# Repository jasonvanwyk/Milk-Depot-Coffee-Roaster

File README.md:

# Milk Depot Coffee Roaster - Precept Systems Project

## Client Information

| Field | Details |
|-------|---------|
| **Client Name** | Quenton (Milk Depot) |
| **Contact** | Via Jason van Wyk |
| **Project** | Coffee Roaster Temperature Monitoring System |

## Project Overview

Custom coffee roasting temperature monitoring system integrating Arduino-based 3-channel thermocouple interface with Artisan roasting software on Raspberry Pi 4. The system reads Bean Temperature (BT), Exhaust Temperature (ET), and Flame Temperature (FT) via MAX31855 amplifiers and displays real-time temperature curves with rate-of-rise calculations.

## Project Scope

1. **Arduino Firmware** - TC4 protocol emulator for 3-channel MAX31855 thermocouple reading
2. **Hardware Integration** - 3x custom K-type thermocouple probes with compression fittings, MAX31855 amplifiers, enclosure
3. **Software Configuration** - Artisan v3.4.0 setup on Raspberry Pi 4 with ArduinoTC4 device
4. **Calibration & Testing** - Probe calibration and first test roast

## Current Status

**See `STATUS.md` for detailed task tracking and current project status.**

### Quick Status
- **Phase:** Hardware Procurement
- **Software:** Complete and tested (firmware + Artisan)
- **Hardware:** Thermocouples on order from GPA Trading (PO P00041)

### Milestones
- [x] Git repository initialized
- [x] Artisan v3.4.0 installed on Raspberry Pi
- [x] Arduino TC4 firmware written and tested
- [x] Helper scripts created (compile, upload, detect, monitor)
- [x] Documentation complete
- [x] Custom thermocouple probes ordered (GPA Trading)
- [ ] Thermocouple probes delivered
- [ ] MAX31855 modules + remaining components procured
- [ ] Hardware assembly in enclosure
- [ ] Sensor calibration
- [ ] First test roast

## Hardware Summary

| Component | Status |
|-----------|--------|
| Raspberry Pi 4 | Owned, Artisan installed |
| Arduino UNO R3 | Owned, firmware tested |
| 3x Custom K-Type Probes | On order (GPA Trading, PO P00041) |
| 3x MAX31855 Modules | To be procured |
| ABS Enclosure | To be procured |
| SSD1306 OLED (optional) | To be procured |

## Temperature Channels

| Channel | Name | Description | Artisan Mapping |
|---------|------|-------------|-----------------|
| 1 | ET | Exhaust/Environment Temperature | Primary ET |
| 2 | BT | Bean Temperature | Primary BT |
| 3 | FT | Flame/Burner Temperature | Extra (ArduinoTC4_34) |

## Key Files

| File | Purpose |
|------|---------|
| `STATUS.md` | **Current project status and task tracking** |
| `RESUME.md` | Quick session resume context |
| `CLAUDE.md` | AI assistant project context |
| `correspondence/` | All client/supplier correspondence |
| `docs/` | Technical documentation and planning |
| `arduino-firmware/` | Arduino sketches (TC4 emulator, temp monitor, etc.) |
| `scripts/` | Helper scripts (compile, upload, detect, monitor) |

## Documentation

All technical documentation is in `docs/`:

| Document | Description |
|----------|-------------|
| [BOM.md](docs/BOM.md) | Bill of Materials with pricing |
| [WIRING.md](docs/WIRING.md) | Wiring diagrams and enclosure layout |
| [ARTISAN_INTEGRATION.md](docs/ARTISAN_INTEGRATION.md) | Artisan configuration guide |
| [SERIAL_PROTOCOL.md](docs/SERIAL_PROTOCOL.md) | TC4 serial communication protocol |
| [ARDUINO_CLI.md](docs/ARDUINO_CLI.md) | Arduino CLI workflow guide |
| [THERMOCOUPLE_SPEC.md](docs/THERMOCOUPLE_SPEC.md) | Thermocouple technical specification |
| [CUSTOM_TC_ORDER_SPEC.md](docs/CUSTOM_TC_ORDER_SPEC.md) | Custom order spec sent to GPA Trading |
| [SHOPPING_LIST.md](docs/SHOPPING_LIST.md) | Printable shopping list with suppliers |

## Quick Start

```bash
# Compile firmware
./scripts/compile.sh arduino-firmware/tc4_emulator

# Upload to Arduino (press RESET if needed)
./scripts/upload.sh arduino-firmware/tc4_emulator

# Monitor serial output
./scripts/monitor.sh

# Detect Arduino boards
./scripts/detect.sh
```

## Workflow Notes

1. Always update `STATUS.md` when tasks are completed or status changes
2. Correspondence goes in `correspondence/` folder with date prefix
3. Technical documents go in `docs/` folder
4. Use git commits with descriptive messages

## License

- Artisan is licensed under GPL-3.0
- This project: MIT License

## Author

Jason van Wyk (jason@precept.co.za) - Precept Systems (Pty) Ltd

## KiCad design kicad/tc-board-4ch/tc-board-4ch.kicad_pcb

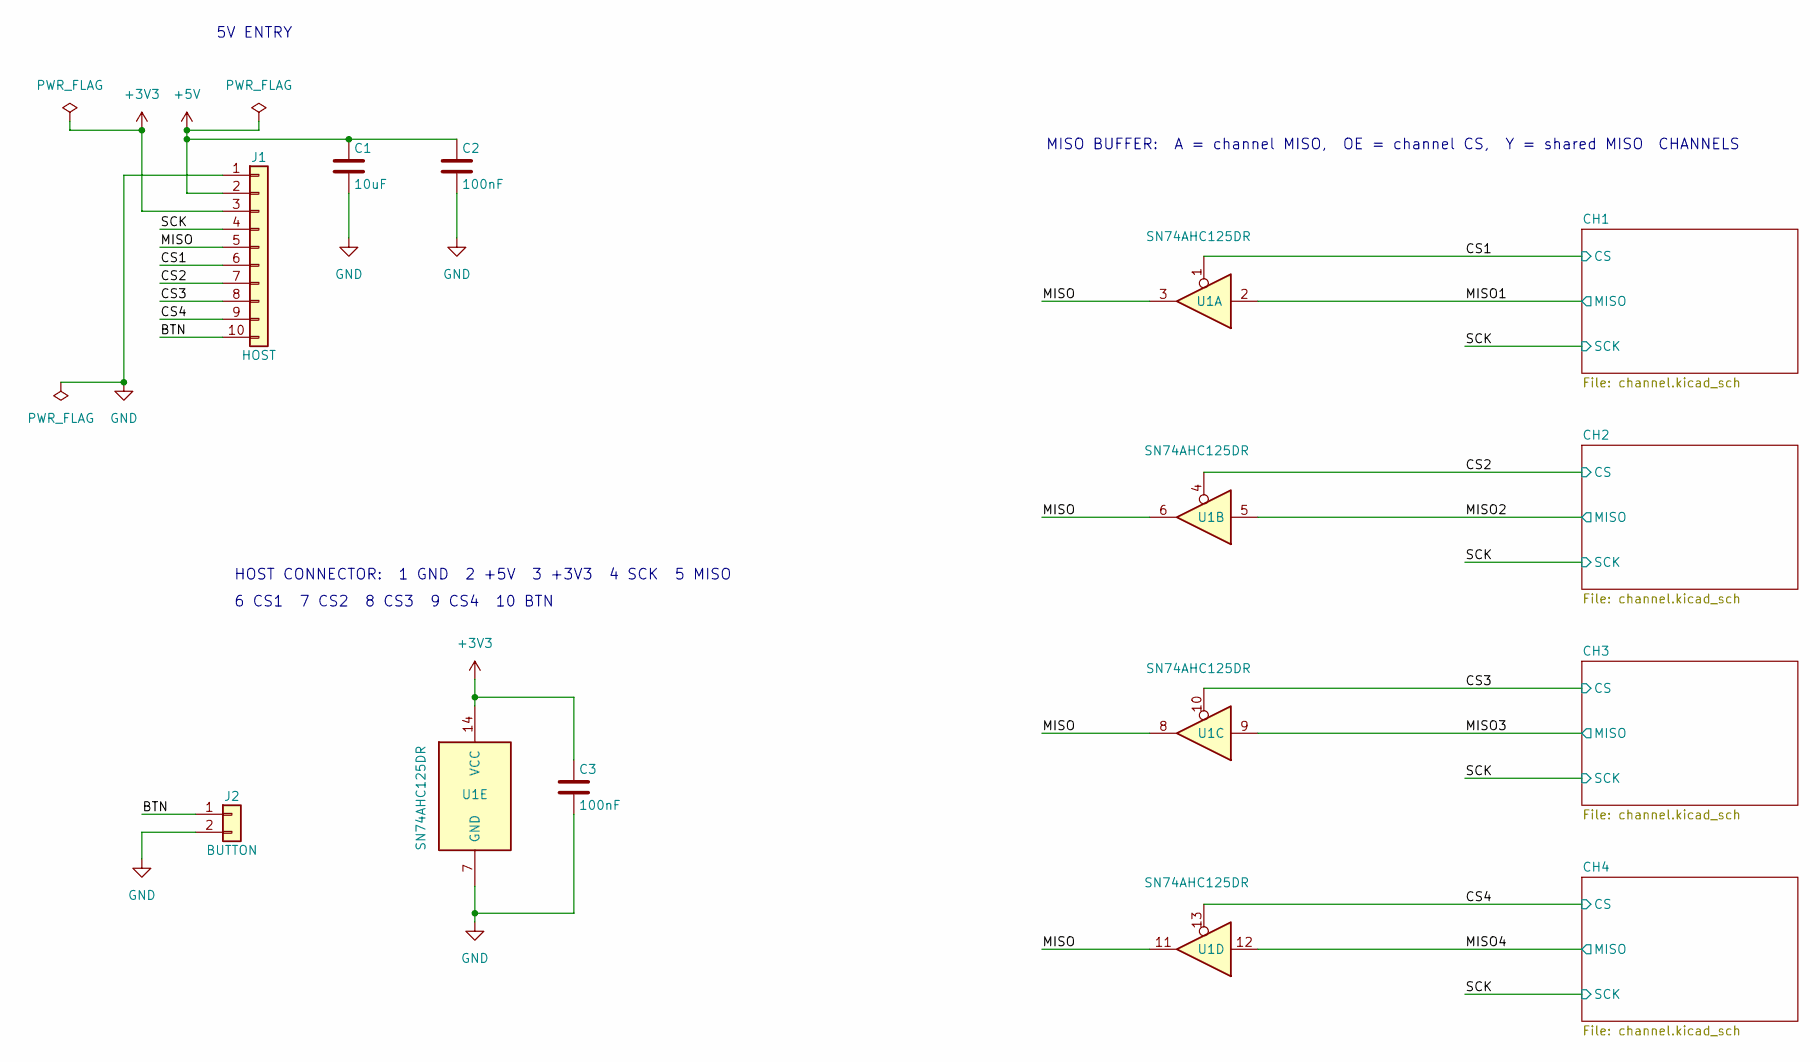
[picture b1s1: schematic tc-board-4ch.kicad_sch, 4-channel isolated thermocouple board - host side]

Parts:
C1: 10uF; C_0805_2012Metric; MPN GRM21BR61C106KE15L
C2, C3: 100nF; C_0805_2012Metric; MPN CL21B104KBCNNNC
J1: HOST; PinHeader_1x10_P2.54mm_Vertical
J2: BUTTON; JST_PH_B2B-PH-K_1x02_P2.00mm_Vertical; MPN B2B-PH-K-S
U1: SN74AHC125DR; SOIC-14_3.9x8.7mm_P1.27mm; MPN SN74AHC125DR

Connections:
+3V3: C3.1, J1.3, U1.14 (VCC); also elsewhere on the board
+5V: C1.1, C2.1, J1.2; also elsewhere on the board
/BTN: J1.10, J2.1
/CS1: J1.6, U1.1; also elsewhere on the board
/CS2: J1.7, U1.4; also elsewhere on the board
/CS3: J1.8, U1.10; also elsewhere on the board
/CS4: J1.9, U1.13; also elsewhere on the board
/MISO: J1.5, U1.3, U1.6, U1.8, U1.11
/MISO1: U1.2; also elsewhere on the board
/MISO2: U1.5; also elsewhere on the board
/MISO3: U1.9; also elsewhere on the board
/MISO4: U1.12; also elsewhere on the board
/SCK: J1.4; also elsewhere on the board
GND: C1.2, C2.2, C3.2, J1.1, J2.2, U1.7 (GND); also elsewhere on the board

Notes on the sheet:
CHANNELS
HOST CONNECTOR: 1 GND 2 +5V 3 +3V3 4 SCK 5 MISO
6 CS1 7 CS2 8 CS3 9 CS4 10 BTN
5V ENTRY
MISO BUFFER: A = channel MISO, OE = channel CS, Y = shared MISO

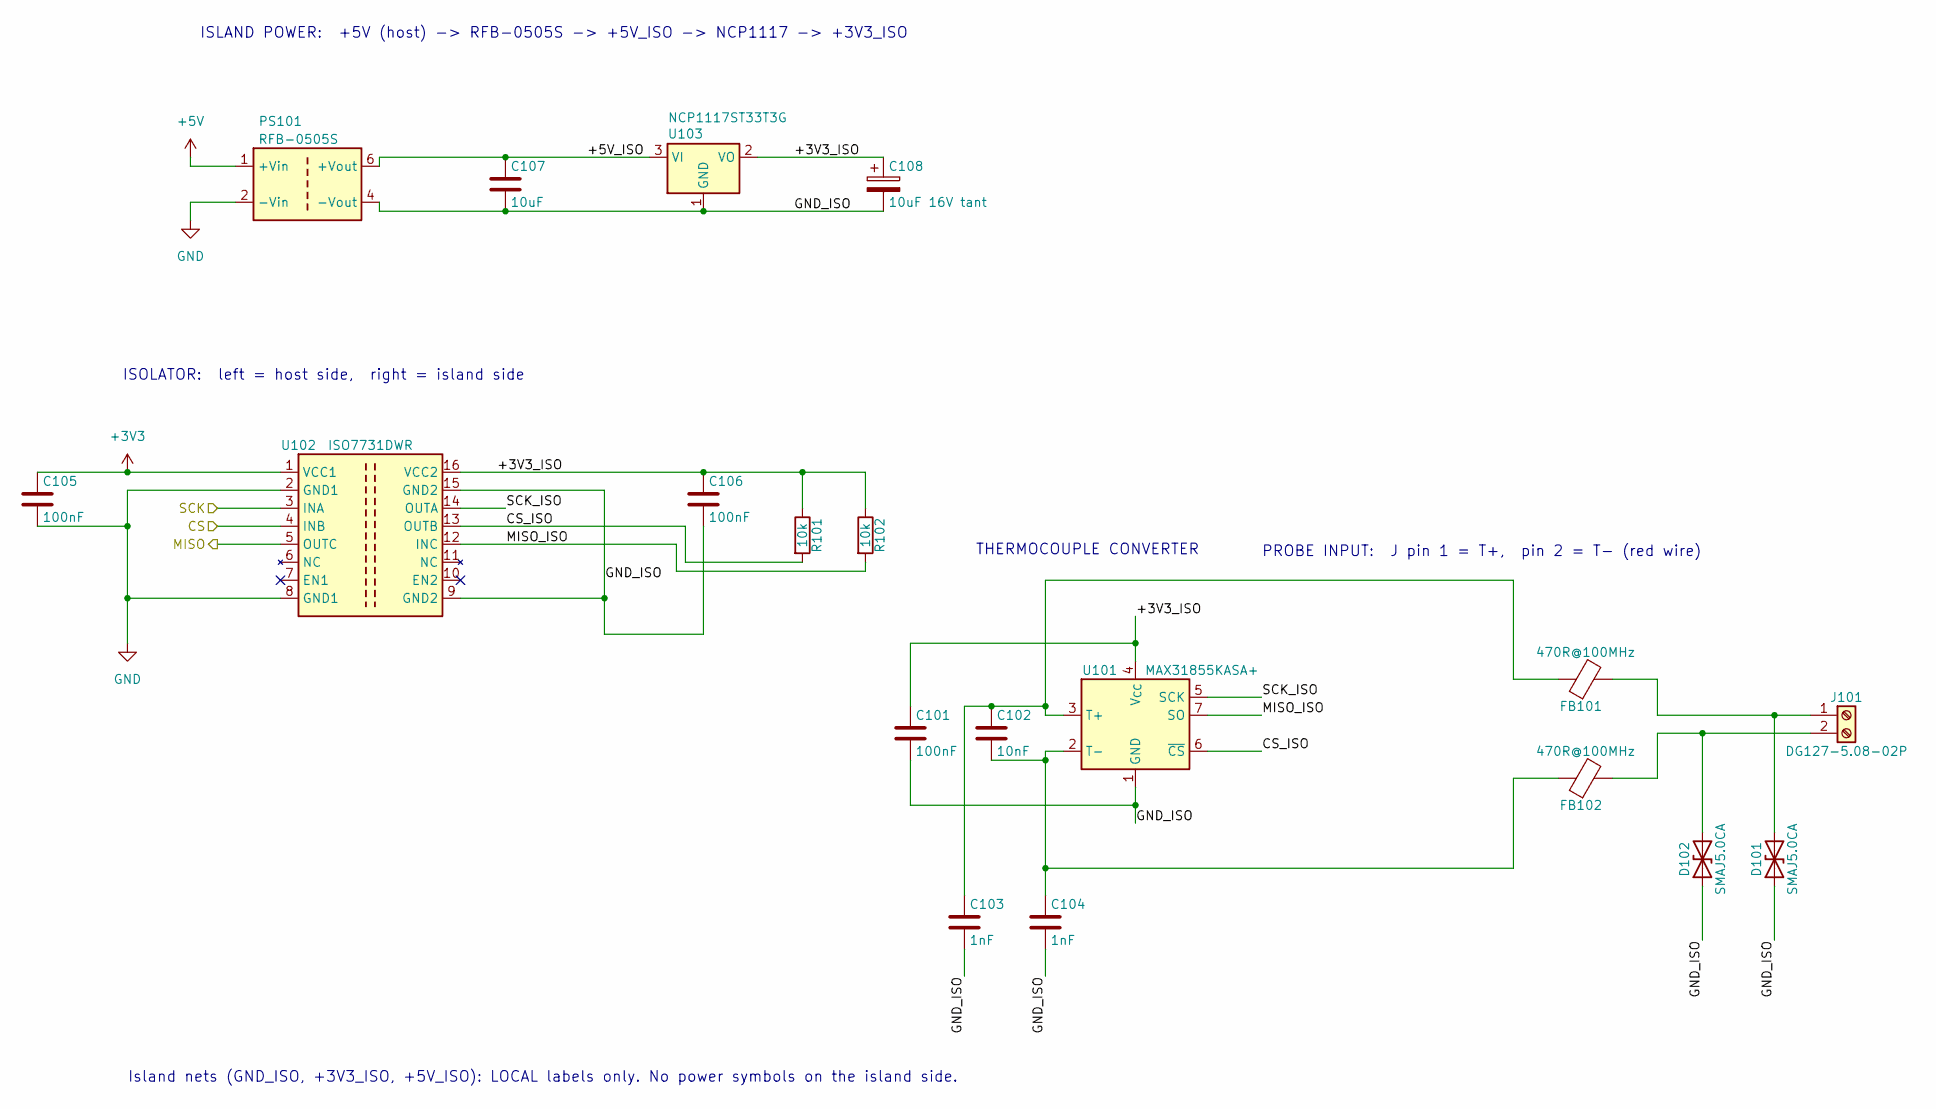
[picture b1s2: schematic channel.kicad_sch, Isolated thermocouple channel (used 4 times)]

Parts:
C101, C105, C106: 100nF; C_0805_2012Metric; MPN CL21B104KBCNNNC
C102: 10nF; C_0805_2012Metric; MPN CL21B103KBANNNC
C103, C104: 1nF; C_0805_2012Metric; MPN CL21B102KBANNNC
C107: 10uF; C_0805_2012Metric; MPN GRM21BR61C106KE15L
C108: 10uF 16V tant; CP_EIA-3528-21_Kemet-B; MPN TPSB106K016R0800
D101, D102: SMAJ5.0CA; D_SMA; MPN SMAJ5.0CA-13-F
FB101, FB102: 470R@100MHz; L_0805_2012Metric; MPN BLM21AG471SN1D
J101: DG127-5.08-02P; Degson_DG127-5.08-02P_1x02_P5.08mm_Horizontal; MPN DG127-5.08-02P-14
PS101: RFB-0505S; Converter_DCDC_TRACO_TMA-05xxS_12xxS_Single_THT; MPN RFB-0505S
R101, R102: 10k; R_0805_2012Metric; MPN RC0805FR-0710KL
U101: MAX31855KASA+; SOIC-8_3.9x4.9mm_P1.27mm; MPN MAX31855KASA+
U102: ISO7731DWR; SOIC-16W_7.5x10.3mm_P1.27mm; MPN ISO7731DWR
U103: NCP1117ST33T3G; SOT-223-3_TabPin2; MPN NCP1117ST33T3G

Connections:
+3V3: C105.1, U102.1 (VCC1); also elsewhere on the board
+5V: PS101.1 (+Vin); also elsewhere on the board
/CH1/+3V3_ISO: C101.1, C106.1, C108.1, R101.1, R102.1, U101.4 (V_{CC}), U102.16 (VCC2), U103.2 (VO)
/CH1/+5V_ISO: C107.1, PS101.6 (+Vout), U103.3 (VI)
/CH1/CS_ISO: R101.2, U101.6 (~CS), U102.13 (OUTB)
/CH1/GND_ISO: C101.2, C103.2, C104.2, C106.2, C107.2, C108.2, D101.1 (A1), D102.1 (A1), PS101.4 (-Vout), U101.1 (GND), U102.9 (GND2), U102.15 (GND2), U103.1 (GND)
/CH1/MISO_ISO: R102.2, U101.7 (SO), U102.12 (INC)
/CH1/SCK_ISO: U101.5 (SCK), U102.14 (OUTA)
/CS1: U102.4 (INB); also elsewhere on the board
/MISO1: U102.5 (OUTC); also elsewhere on the board
/SCK: U102.3 (INA); also elsewhere on the board
GND: C105.2, PS101.2 (-Vin), U102.2 (GND1), U102.8 (GND1); also elsewhere on the board
unnamed: D101.2 (A2), FB101.2, J101.1
unnamed: D102.2 (A2), FB102.2, J101.2
unnamed: C102.1, C103.1, FB101.1, U101.3 (T+)
unnamed: C102.2, C104.1, FB102.1, U101.2 (T-)

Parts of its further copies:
C201, C205, C206, C301, C305, C306, C401, C405, C406: 100nF; C_0805_2012Metric; MPN CL21B104KBCNNNC
C202, C302, C402: 10nF; C_0805_2012Metric; MPN CL21B103KBANNNC
C203, C204, C303, C304, C403, C404: 1nF; C_0805_2012Metric; MPN CL21B102KBANNNC
C207, C307, C407: 10uF; C_0805_2012Metric; MPN GRM21BR61C106KE15L
C208, C308, C408: 10uF 16V tant; CP_EIA-3528-21_Kemet-B; MPN TPSB106K016R0800
D201, D202, D301, D302, D401, D402: SMAJ5.0CA; D_SMA; MPN SMAJ5.0CA-13-F
FB201, FB202, FB301, FB302, FB401, FB402: 470R@100MHz; L_0805_2012Metric; MPN BLM21AG471SN1D
J201, J301, J401: DG127-5.08-02P; Degson_DG127-5.08-02P_1x02_P5.08mm_Horizontal; MPN DG127-5.08-02P-14
PS201, PS301, PS401: RFB-0505S; Converter_DCDC_TRACO_TMA-05xxS_12xxS_Single_THT; MPN RFB-0505S
R201, R202, R301, R302, R401, R402: 10k; R_0805_2012Metric; MPN RC0805FR-0710KL
U201, U301, U401: MAX31855KASA+; SOIC-8_3.9x4.9mm_P1.27mm; MPN MAX31855KASA+
U202, U302, U402: ISO7731DWR; SOIC-16W_7.5x10.3mm_P1.27mm; MPN ISO7731DWR
U203, U303, U403: NCP1117ST33T3G; SOT-223-3_TabPin2; MPN NCP1117ST33T3G

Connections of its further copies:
+3V3: C205.1, C305.1, C405.1, U202.1 (VCC1), U302.1 (VCC1), U402.1 (VCC1); also elsewhere on the board
+5V: PS201.1 (+Vin), PS301.1 (+Vin), PS401.1 (+Vin); also elsewhere on the board
/CH2/+3V3_ISO: C201.1, C206.1, C208.1, R201.1, R202.1, U201.4 (V_{CC}), U202.16 (VCC2), U203.2 (VO)
/CH2/+5V_ISO: C207.1, PS201.6 (+Vout), U203.3 (VI)
/CH2/CS_ISO: R201.2, U201.6 (~CS), U202.13 (OUTB)
/CH2/GND_ISO: C201.2, C203.2, C204.2, C206.2, C207.2, C208.2, D201.1 (A1), D202.1 (A1), PS201.4 (-Vout), U201.1 (GND), U202.9 (GND2), U202.15 (GND2), U203.1 (GND)
/CH2/MISO_ISO: R202.2, U201.7 (SO), U202.12 (INC)
/CH2/SCK_ISO: U201.5 (SCK), U202.14 (OUTA)
/CH3/+3V3_ISO: C301.1, C306.1, C308.1, R301.1, R302.1, U301.4 (V_{CC}), U302.16 (VCC2), U303.2 (VO)
/CH3/+5V_ISO: C307.1, PS301.6 (+Vout), U303.3 (VI)
/CH3/CS_ISO: R301.2, U301.6 (~CS), U302.13 (OUTB)
/CH3/GND_ISO: C301.2, C303.2, C304.2, C306.2, C307.2, C308.2, D301.1 (A1), D302.1 (A1), PS301.4 (-Vout), U301.1 (GND), U302.9 (GND2), U302.15 (GND2), U303.1 (GND)
/CH3/MISO_ISO: R302.2, U301.7 (SO), U302.12 (INC)
/CH3/SCK_ISO: U301.5 (SCK), U302.14 (OUTA)
/CH4/+3V3_ISO: C401.1, C406.1, C408.1, R401.1, R402.1, U401.4 (V_{CC}), U402.16 (VCC2), U403.2 (VO)
/CH4/+5V_ISO: C407.1, PS401.6 (+Vout), U403.3 (VI)
/CH4/CS_ISO: R401.2, U401.6 (~CS), U402.13 (OUTB)
/CH4/GND_ISO: C401.2, C403.2, C404.2, C406.2, C407.2, C408.2, D401.1 (A1), D402.1 (A1), PS401.4 (-Vout), U401.1 (GND), U402.9 (GND2), U402.15 (GND2), U403.1 (GND)
/CH4/MISO_ISO: R402.2, U401.7 (SO), U402.12 (INC)
/CH4/SCK_ISO: U401.5 (SCK), U402.14 (OUTA)
/CS2: U202.4 (INB); also elsewhere on the board
/CS3: U302.4 (INB); also elsewhere on the board
/CS4: U402.4 (INB); also elsewhere on the board
/MISO2: U202.5 (OUTC); also elsewhere on the board
/MISO3: U302.5 (OUTC); also elsewhere on the board
/MISO4: U402.5 (OUTC); also elsewhere on the board
/SCK: U202.3 (INA), U302.3 (INA), U402.3 (INA); also elsewhere on the board
GND: C205.2, C305.2, C405.2, PS201.2 (-Vin), PS301.2 (-Vin), PS401.2 (-Vin), U202.2 (GND1), U202.8 (GND1), U302.2 (GND1), U302.8 (GND1), U402.2 (GND1), U402.8 (GND1); also elsewhere on the board
unnamed: D201.2 (A2), FB201.2, J201.1
unnamed: D202.2 (A2), FB202.2, J201.2
unnamed: D301.2 (A2), FB301.2, J301.1
unnamed: D302.2 (A2), FB302.2, J301.2
unnamed: D401.2 (A2), FB401.2, J401.1
unnamed: D402.2 (A2), FB402.2, J401.2
unnamed: C202.1, C203.1, FB201.1, U201.3 (T+)
unnamed: C202.2, C204.1, FB202.1, U201.2 (T-)
unnamed: C302.1, C303.1, FB301.1, U301.3 (T+)
unnamed: C302.2, C304.1, FB302.1, U301.2 (T-)
unnamed: C402.1, C403.1, FB401.1, U401.3 (T+)
unnamed: C402.2, C404.1, FB402.1, U401.2 (T-)

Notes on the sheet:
ISOLATOR: left = host side, right = island side
Island nets (GND_ISO, +3V3_ISO, +5V_ISO): LOCAL labels only. No power symbols on the island side.
ISLAND POWER: +5V (host) -> RFB-0505S -> +5V_ISO -> NCP1117 -> +3V3_ISO
THERMOCOUPLE CONVERTER
PROBE INPUT: J pin 1 = T+, pin 2 = T- (red wire)

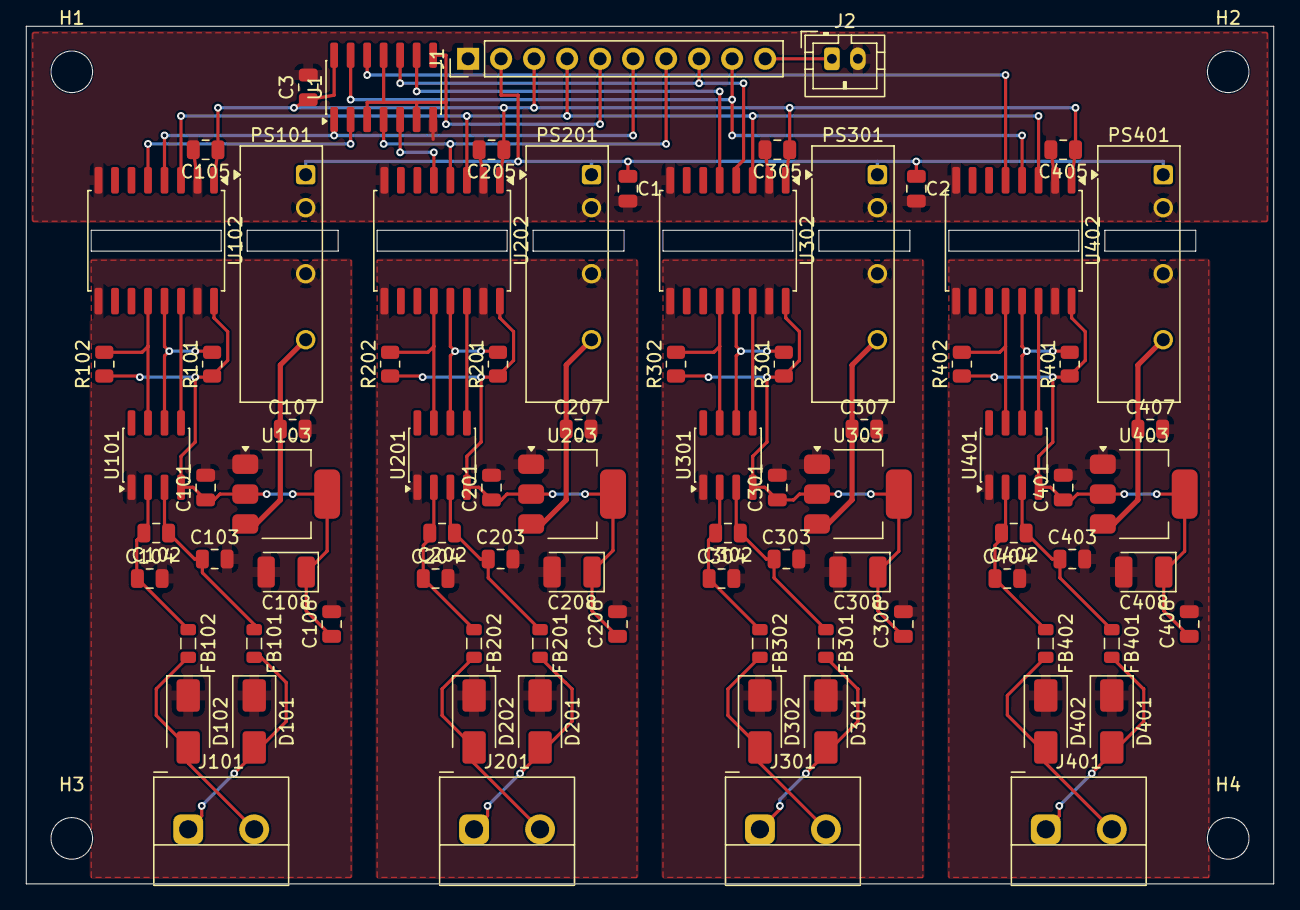
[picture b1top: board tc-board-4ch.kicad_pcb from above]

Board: 2 copper layers, 96.0 x 66.0 mm, 86 parts (0 on the bottom side), 54 nets.

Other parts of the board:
H1, H2, H3, H4: MountingHole_3.2mm_M3

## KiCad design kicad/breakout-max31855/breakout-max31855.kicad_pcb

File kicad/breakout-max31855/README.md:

# MD-TC-BRK v1.0 — MAX31855 K-Type Thermocouple Breakout

Custom breakout forked from **SparkFun DEV-13266** (MAX31855K Thermocouple Breakout), ported Eagle → KiCad 10 and adapted for the Milk Depot Coffee Roaster signal chain.

Client: Quenton (Milk Depot)
Design owner: Precept Systems (Pty) Ltd — Jason van Wyk
Status at creation: 2026-04-21 — **pre-import scaffold**. Eagle source vendored, KiCad project not yet generated.

## Board identity

| Field | Value |
|---|---|
| Board ID (silkscreen) | `MD-TC-BRK v1.0` |
| Project role | 1-of-3 breakouts on Nano stripboard (BT, ET, FT channels) |
| Licence | CC-BY-SA 4.0 (derivative) |
| Attribution | Fork of SparkFun DEV-13266 — https://github.com/sparkfun/Thermocouple_Breakout-MAX31855K |
| Upstream licence | CC-BY-SA 4.0 — preserved at `eagle-source/LICENSE-upstream.md` |

## Architecture context (short)

The Milk Depot roaster uses three K-type probes (Bean, Exhaust, Flame) feeding an Arduino Nano 5V via three of these breakouts on a stripboard. A dedicated NCP1117ST33T3G LDO supplies 3.3V to the breakouts from the stripboard; SPI is level-shifted by resistor dividers (SCK 1k/1.8k shared, CS 10k/18k per channel). Shields terminate at the probe end only. See `kicad-coffee-roaster` tool repo `RESUME.md` for the full locked spec.

## Repository layout

```
breakout-max31855/
├── README.md                                     ← this file
├── eagle-source/                                 ← upstream reference, DO NOT EDIT
│   ├── SparkFun_Thermocouple_Breakout.sch       ← Eagle XML — import source
│   ├── SparkFun_Thermocouple_Breakout.brd       ← Eagle board — optional PCB ref
│   └── LICENSE-upstream.md                       ← SparkFun CC-BY-SA 4.0 notice
└── (KiCad files will be generated by the import step below)
```

## KiCad 10 Eagle import — step-by-step

The import is a KiCad GUI operation; `kicad-cli` has no Eagle import in v10.0.1.

### 1. Launch KiCad and run the import

```bash
kicad   # or GDK_BACKEND=x11 kicad  if Wayland decoration clips dialogs
```

In KiCad's project manager:

1. **File → Import → Non-KiCad Project → Eagle**
2. Select source: `breakout-max31855/eagle-source/SparkFun_Thermocouple_Breakout.sch`
3. Select destination: `breakout-max31855/` (same folder as this README)
4. Project name: `breakout-max31855`
5. Click **Import**

KiCad will generate `breakout-max31855.kicad_pro`, `.kicad_sch`, `.kicad_pcb` (and possibly `.kicad_sym` / `.pretty/` for unmapped symbols/footprints).

### 2. Tell Claude to run phase-2 cleanup

Once the import finishes, return to the `kicad-coffee-roaster` tool session and say "import done, run phase 2" — Claude will:

- Set the title block (title, company, author, revision, date, comments with licence & attribution)
- Set page size to **A4 landscape**
- Link the shared custom library (`../libs/milk-depot.kicad_sym` + `../libs/milk-depot.pretty`) via the project's `sym-lib-table` / `fp-lib-table`
- Run `kicad-cli sch erc` as a post-import sanity check

## Planned forks from upstream (5 changes)

Tracked as the "design deltas" from SparkFun DEV-13266. Each is a separate working session after phase-2 cleanup completes.

- [ ] **1. Footprint swap** — MAX31855K generic → **MAX31855KASA+** (genuine Maxim SOIC-8) using the symbol in `../libs/milk-depot.kicad_sym`.
- [ ] **2. Thermocouple connector** — Replace SparkFun's `PCB_THERMOCOUPLE` pads with **DG127-5.08-02P** (Mantech 15M0713) 2-pole 5.08 mm screw terminal. Verify pin 1 orientation against Degson datasheet.
- [ ] **3. Passive upsize** — 0603 → **0805** throughout (matches DigiKey #122880837 stock convention). C1 100 nF X7R, C2 10 nF X7R, L1/L2 470 Ω @ 100 MHz, R1 10 kΩ.
- [ ] **4. DNP footprints** — Add (do-not-populate by default):
  - C3, C4 (1 nF X7R 0805) — T+/T− common-mode caps
  - D1, D2 (5.6 V bidirectional TVS, SMA/SMB) — ESD/surge clamp at screw terminal
  - M3 chassis-bond mounting hole: 10 nF Y1 cap + 1 MΩ bleed resistor (both DNP for soft-bond option at bring-up)
- [ ] **5. Silkscreen + title block** — Board ID, attribution, licence, polarity warnings per locked spec:
  - `MD-TC-BRK v1.0`
  - `CC-BY-SA 4.0 / fork of SparkFun MAX31855K`
  - `Red = NEGATIVE` next to DG127 terminal
  - `+` / `−` markers on DG127 pads
  - `3.3V ONLY` next to VCC pin on JP1 header
  - Pin 1 dot on U1, JP1, J1

## Mechanical targets

- Screw terminal J1 on one long edge, 6-pin header JP1 on the opposite long edge, 20–25 mm apart.
- Preserve SparkFun's JP1 pinout exactly: `GND, VCC, SCK, MISO, NC, CS` — this keeps compatibility with SparkFun's reference wiring diagrams and any DEV-13266 sockets on the stripboard.
- 4× unplated M3 mounting holes (check clearance against the DG127 body and U1).
- Target PCB: 2-layer, JLCPCB-standard (6 mil/6 mil trace/space, 0.3 mm via).

## Bring-up plan (for later reference)

Once fabbed, a genuine **SparkFun DEV-13266** (~$15, to be ordered) acts as the golden reference. First power-up reads the same K-type probe on both boards in parallel; agreement within 0.5°C validates our fork.

## Related docs (outside this folder)

- `../../docs/BOM.md` — project-wide BOM (will need update to carry MD-TC-BRK v1.0 line items at fab time)
- `../../docs/THERMOCOUPLE_SPEC.md` — K-type probe spec, GPA Trading PO P00041
- `~/tools/kicad-coffee-roaster/` — design companion tool repo, holds prior-art research, reference designs (including Adafruit for comparison), and the locked electrical spec
- `~/tools/kicad-coffee-roaster/docs/reference-designs/sparkfun-max31855k/` — full vendored SparkFun upstream (Hardware, Libraries, README, LICENSE)

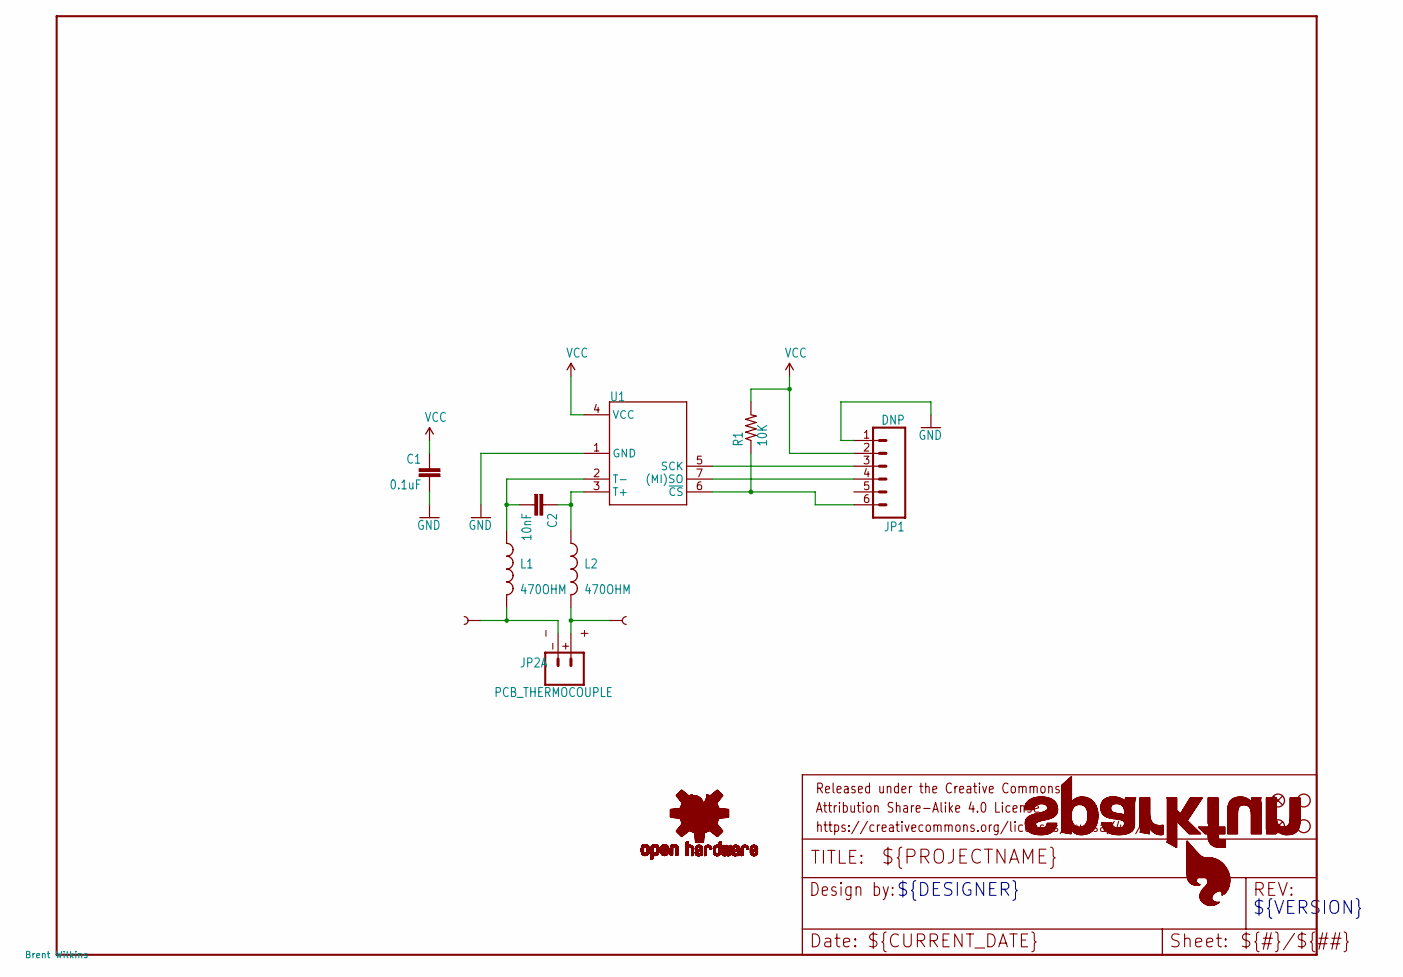
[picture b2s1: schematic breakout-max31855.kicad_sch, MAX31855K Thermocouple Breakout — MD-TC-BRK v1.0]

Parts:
C1: 0.1uF; 0603-CAP
C2: 10nF; 0603-CAP
FID1, FID2: FIDUCIAL1X2; FIDUCIAL-1X2
FRAME1: >VERSION; CREATIVE_COMMONS
JP1: DNP; 1X06
JP2: PCB_THERMOCOUPLE; PCC-SMP
L1, L2: 470OHM; 0603
LOGO1, LOGO4: OSHW-LOGOS; OSHW-LOGO-S
LOGO2, LOGO3: SFE_LOGO_NAME_FLAME.1_INCH; SFE_LOGO_NAME_FLAME_.1
R1: 10K; 0603-RES
STANDOFF1, STANDOFF4: STAND-OFF
TP1, TP2: TEST-POINTTP_15TH_THRU; TP_15TH
U1: MAX31855K; SOIC8

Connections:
GND: C1.2, JP1.1, U1.1 (GND)
unnamed: JP1.3, U1.5 (SCK)
unnamed: JP1.4, U1.7 ((MI)SO)
unnamed: C2.2, L1.1, U1.2 (T-)
unnamed: JP2.+, L2.2, TP1.P$1
unnamed: JP2.-, L1.2, TP2.P$1
unnamed: C2.1, L2.1, U1.3 (T+)
unnamed: JP1.6, R1.1, U1.6 (~CS)
VCC: C1.1, JP1.2, R1.2, U1.4 (VCC)

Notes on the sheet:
${DESIGNER}
${VERSION}

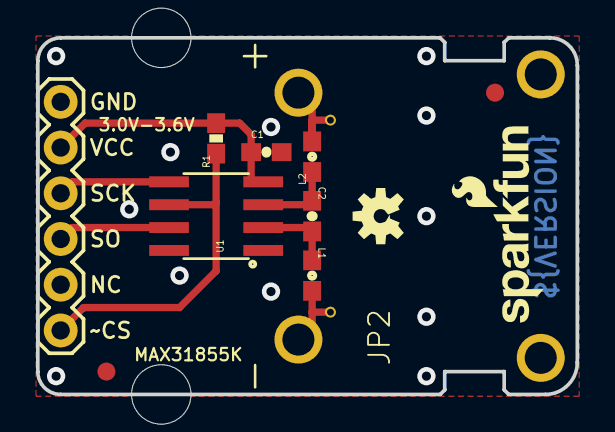
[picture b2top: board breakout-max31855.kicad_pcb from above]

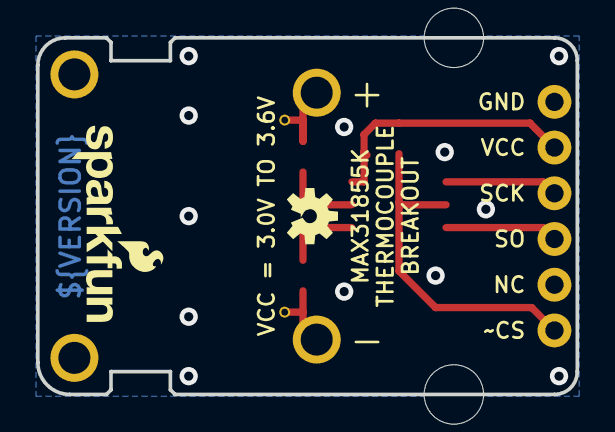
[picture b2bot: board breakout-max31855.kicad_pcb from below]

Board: 2 copper layers, 30.0 x 19.8 mm, 19 parts (2 on the bottom side), 9 nets.

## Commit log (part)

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2025-11-10 Add GitHub repository information to README

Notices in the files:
kicad/breakout-max31855/breakout-max31855.kicad_sch:
Derivative of SparkFun DEV-13266 — CC-BY-SA 4.0
Released under the Creative Commons
https://creativecommons.org/licenses/by-sa/4.0
parts and their libraries:
Released under the Creative Commons Attribution Share-Alike 4.0 License
